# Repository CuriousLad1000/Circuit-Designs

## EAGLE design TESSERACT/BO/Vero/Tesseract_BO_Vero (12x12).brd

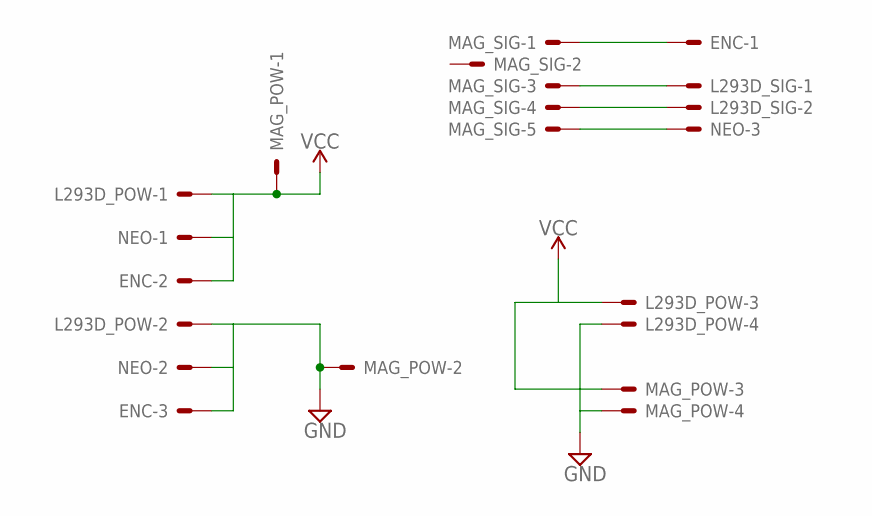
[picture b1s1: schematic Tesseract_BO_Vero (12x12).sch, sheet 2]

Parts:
ENC: JST-XH-03-PIN-LONG-PAD; JST-XH-03-PACKAGE-LONG-PAD
L293D_POW: JST-XH-04-PIN-LONG-PAD; JST-XH-04-PACKAGE-LONG-PAD
L293D_SIG: JST-XH-02-PIN-LONG-PAD; JST-XH-02-PACKAGE-LONG-PAD
MAG_POW: JST-XH-04-PIN-LONG-PAD; JST-XH-04-PACKAGE-LONG-PAD
MAG_SIG: JST-XH-05-PIN-LONG-PAD; JST-XH-05-PACKAGE-LONG-PAD
NEO: JST-XH-03-PIN-LONG-PAD; JST-XH-03-PACKAGE-LONG-PAD

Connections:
5V_GND: ENC.3, L293D_POW.2, MAG_POW.2, NEO.2
5V_VCC: ENC.2, L293D_POW.1, MAG_POW.1, NEO.1
12V_GND: L293D_POW.4, MAG_POW.4
12V_VCC: L293D_POW.3, MAG_POW.3
PIN3: ENC.1, MAG_SIG.1
PIN5: L293D_SIG.1, MAG_SIG.3
PIN6: L293D_SIG.2, MAG_SIG.4
PIN7: MAG_SIG.5, NEO.3

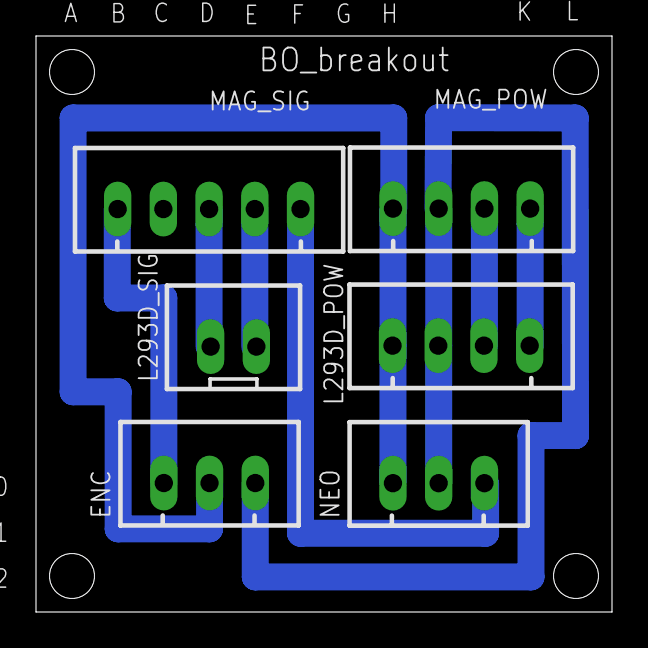
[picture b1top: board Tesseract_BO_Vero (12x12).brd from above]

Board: 2 copper layers, 32.0 x 32.0 mm, 7 parts (0 on the bottom side), 8 nets.

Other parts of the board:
U$15: 12X12

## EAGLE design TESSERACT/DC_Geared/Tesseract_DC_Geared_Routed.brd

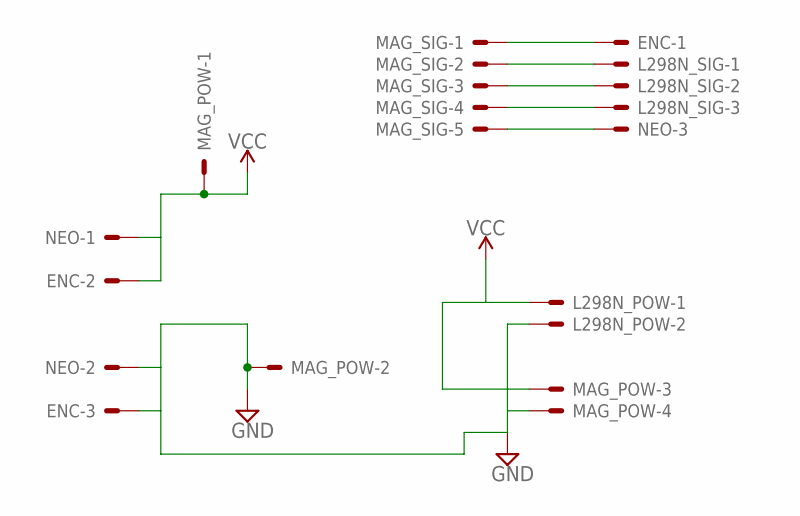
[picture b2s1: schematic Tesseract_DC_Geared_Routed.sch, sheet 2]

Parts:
ENC: JST-XH-03-PIN-LONG-PAD; JST-XH-03-PACKAGE-LONG-PAD
L298N_POW: JST-XH-02-PIN-LONG-PAD; JST-XH-02-PACKAGE-LONG-PAD
L298N_SIG: JST-XH-03-PIN-LONG-PAD; JST-XH-03-PACKAGE-LONG-PAD
MAG_POW: JST-XH-04-PIN-LONG-PAD; JST-XH-04-PACKAGE-LONG-PAD
MAG_SIG: JST-XH-05-PIN-LONG-PAD; JST-XH-05-PACKAGE-LONG-PAD
NEO: JST-XH-03-PIN-LONG-PAD; JST-XH-03-PACKAGE-LONG-PAD

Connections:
5V_GND: ENC.3, L298N_POW.2, MAG_POW.2, MAG_POW.4, NEO.2
5V_VCC: ENC.2, MAG_POW.1, NEO.1
12V_VCC: L298N_POW.1, MAG_POW.3
PIN3: ENC.1, MAG_SIG.1
PIN4: L298N_SIG.1, MAG_SIG.2
PIN5: L298N_SIG.2, MAG_SIG.3
PIN6: L298N_SIG.3, MAG_SIG.4
PIN7: MAG_SIG.5, NEO.3

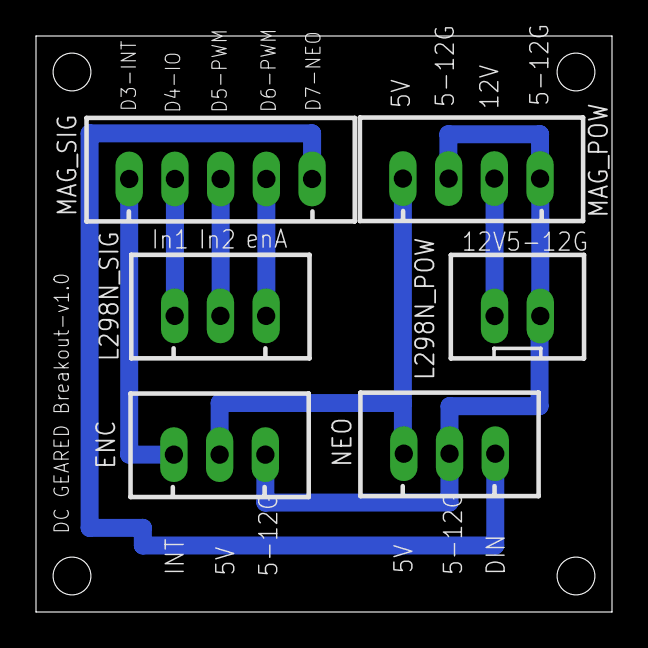
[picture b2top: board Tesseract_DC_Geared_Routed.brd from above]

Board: 2 copper layers, 32.0 x 32.0 mm, 7 parts (0 on the bottom side), 8 nets.

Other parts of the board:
U$15: 12X12

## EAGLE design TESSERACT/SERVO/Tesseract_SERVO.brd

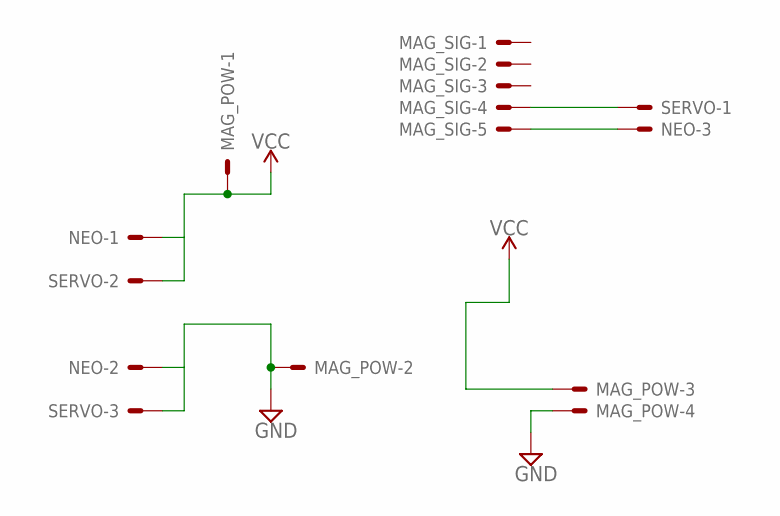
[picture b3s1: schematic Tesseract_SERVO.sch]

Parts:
MAG_POW: JST-XH-04-PIN-LONG-PAD; JST-XH-04-PACKAGE-LONG-PAD
MAG_SIG: JST-XH-05-PIN-LONG-PAD; JST-XH-05-PACKAGE-LONG-PAD
NEO: JST-XH-03-PIN-LONG-PAD; JST-XH-03-PACKAGE-LONG-PAD
SERVO: JST-XH-03-PIN-LONG-PAD; JST-XH-03-PACKAGE-LONG-PAD

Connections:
5V_GND: MAG_POW.2, NEO.2, SERVO.3
5V_VCC: MAG_POW.1, NEO.1, SERVO.2
12V_GND: MAG_POW.4
12V_VCC: MAG_POW.3
PIN6: MAG_SIG.4, SERVO.1
PIN7: MAG_SIG.5, NEO.3

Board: 2 copper layers, 4 parts (0 on the bottom side), 4 nets, no tracks yet.

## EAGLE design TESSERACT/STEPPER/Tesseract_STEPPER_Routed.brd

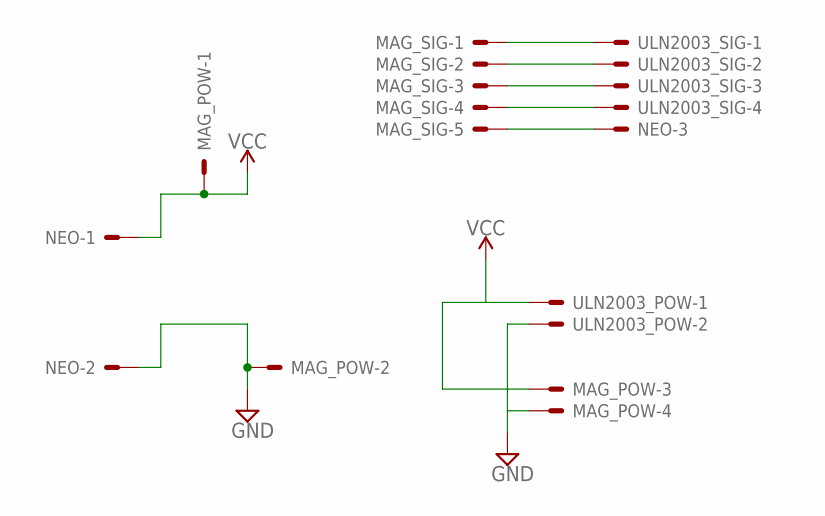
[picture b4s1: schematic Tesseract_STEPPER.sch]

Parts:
MAG_POW: JST-XH-04-PIN-LONG-PAD; JST-XH-04-PACKAGE-LONG-PAD
MAG_SIG: JST-XH-05-PIN-LONG-PAD; JST-XH-05-PACKAGE-LONG-PAD
NEO: JST-XH-03-PIN-LONG-PAD; JST-XH-03-PACKAGE-LONG-PAD
ULN2003_POW: JST-XH-02-PIN-LONG-PAD; JST-XH-02-PACKAGE-LONG-PAD
ULN2003_SIG: JST-XH-04-PIN-LONG-PAD; JST-XH-04-PACKAGE-LONG-PAD

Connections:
5V_GND: MAG_POW.2, NEO.2
5V_VCC: MAG_POW.1, NEO.1
12V_GND: MAG_POW.4, ULN2003_POW.2
12V_VCC: MAG_POW.3, ULN2003_POW.1
PIN3: MAG_SIG.1, ULN2003_SIG.1
PIN4: MAG_SIG.2, ULN2003_SIG.2
PIN5: MAG_SIG.3, ULN2003_SIG.3
PIN6: MAG_SIG.4, ULN2003_SIG.4
PIN7: MAG_SIG.5, NEO.3

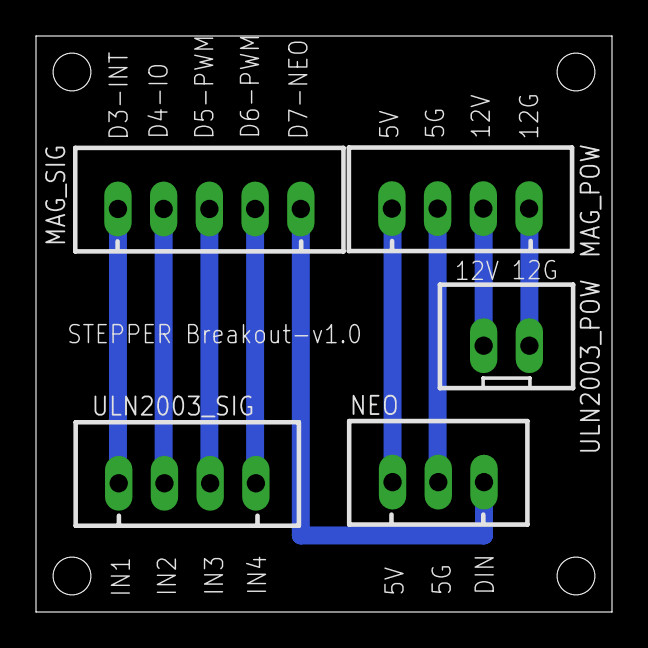
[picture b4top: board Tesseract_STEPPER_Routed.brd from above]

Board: 2 copper layers, 32.0 x 32.0 mm, 6 parts (0 on the bottom side), 9 nets.

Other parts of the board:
U$15: 12X12

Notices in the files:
parts and their libraries:
SparkFun-PowerSymbols: Licensing: Creative Commons ShareAlike 4.0 International - https://creativecommons.org/licenses/by-sa/4.0
